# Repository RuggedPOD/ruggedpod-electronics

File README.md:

# RuggedPOD Electronic Design

This repository contains design for electronics, cables and connectors design.

Electonics design is done under [KiCad](http://kicad-pcb.org/), an open source electronics design automation suite.

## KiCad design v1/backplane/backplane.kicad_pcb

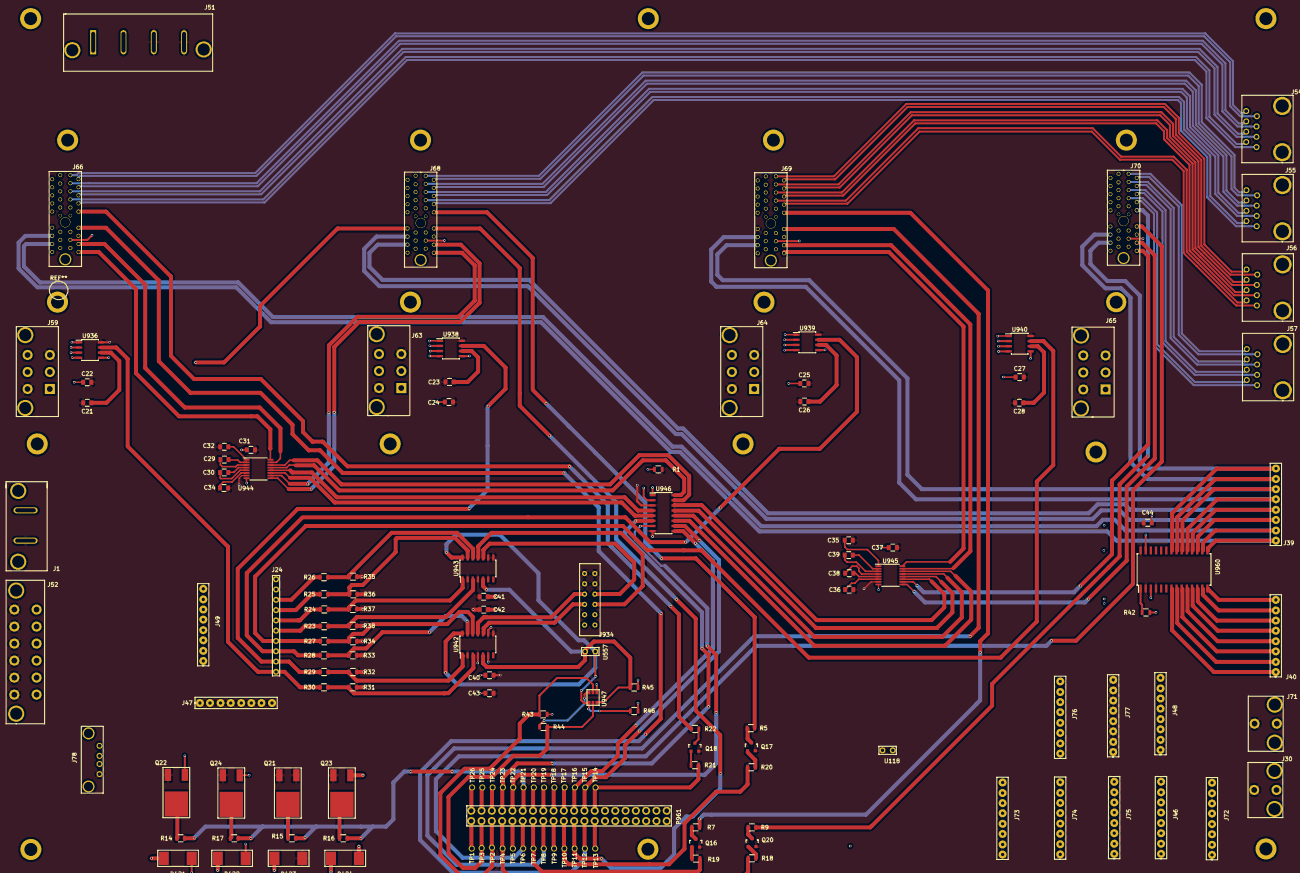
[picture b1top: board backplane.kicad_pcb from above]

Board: 4 copper layers, 141 parts (0 on the bottom side), 158 nets.

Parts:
C21, C23, C26, C28: 1n; C_0805
C22, C24, C25, C27, C29, C30, C31, C32, C34, C35, C36, C37, C38, C39, C40, C43: 0.1u; C_0805
C41, C42: 10u; C_0805
C44: 100n; C_0805
D421, D422, D423, D424: B520C-13-F; B520C
J1: Molex-1720420201; Molex172042-0201
J24: 10_Pin_Header; XG8V-1031
J30, J71: Molex-46999-0126; Molex46999-0126
J39, J40, J46, J47, J48, J49, J72, J73, J74, J75, J76, J77: SWITCH; XG8
J51: MOLEX172042-0402; Molex172042-0402
J52: MOLEX-39-28-9128; Molex_39-28-9128
J54, J55, J56, J57: MOLEX_85506-5001; Molex_85506-5001
J59, J63, J64, J65: 15-24-7060Molex; MOLEX15247060
J66, J68, J69, J70: FCI10018783-10000MLF; FCI_10018783-10000MLF
J78: 1734366-1; 1734366-1USB
J934: SWITCH934; FCI861400122YO2
P961: 0702464001; FCI702464001
Q16, Q17, Q18, Q20: bsr14; SOT-23
Q21, Q22, Q23, Q24: MJD112TF; MJD112
R1: 51; R_0805
R5, R7, R9, R22: 470; R_0805
R14, R15, R16, R17: 1K; R_0805
R18, R19, R20, R21: 2K; R_0805
R23, R24, R25, R26, R27, R28, R29, R30, R31, R32, R33, R34, R35, R36, R37, R38, R42: 10k; R_0805
R43, R44, R45, R46: 2.2K; R_0805
TP1, TP2, TP3, TP4, TP5, TP6, TP7, TP8, TP9, TP10, TP11, TP12, TP13, TP14, TP15, TP16, TP17, TP18, TP19, TP20, TP21, TP22, TP23, TP24, TP25, TP26: TP
U118, U557: Controler_Rasberry; XG8V-0231
U936, U938, U939, U940: ACS712ELCTR-20A-T; SOIC-8_3.9x4.9mm_Pitch1.27mm
U942, U943: MCP3424; SOIC-14_3.9x8.7mm_Pitch1.27mm
U944, U945: MAX3232; TSSOP-16_4.4x5mm_Pitch0.65mm
U946: MAX399; SOIC-16_3.9x9.9mm_Pitch1.27mm
U947: FDC6301N
U960: MCP23017; SOIC-28_7.5x17.9mm_Pitch1.27mm

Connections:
5VCC: C22.1, C24.1, C25.1, C27.1, C40.1, C41.1, C42.1, C43.1, C44.1, J24.9, J46.1, J46.2, J46.3, J46.4, J46.5, J46.6, J46.7, J46.8, J52.1, J52.3, J52.5, J71.1, J78.1, J934.1, J934.2, J934.7, J934.8, R42.1, R45.2, R46.1, U118.2, U936.1, U938.1, U939.1, U940.1, U960.3, U960.27
12VCC: D421.1, D422.1, D423.1, D424.1, J30.1, J48.1, J48.2, J48.3, J48.4, J48.5, J48.6, J48.7, J48.8, J52.2, J52.4, J52.6, J66.30, J68.30, J69.30, J70.30
24V_1: J59.1, J59.4, U936.4, U936.5
24V_2: J63.1, J63.4, U938.4, U938.5
24V_3: J64.1, J64.4, U939.4, U939.5
24V_4: J65.1, J65.4, U940.4, U940.5
24V_acdc: J1.1, J51.1, J51.2, U936.2, U936.3, U938.2, U938.3, U939.2, U939.3, U940.2, U940.3
+3V3: C31.1, C37.1, R1.1, R43.1, U944.8, U945.8, U946.1, U946.2, U947.3
APump_GND: D421.2, J66.23, Q22.3
APump_PWM: J39.1, J66.27, U960.15
APump_Sense: J39.2, J66.31, U960.16
A_Adr0: J934.10, U942.11
A_Adr1: J934.9, U942.10
A_ON/OFF: J66.20, R22.1
A_RESET: J66.24, P961.12, TP12.1
A_RX: J66.32, U944.15
A_RX_TTL: U944.13, U946.16
A_TD0+: J54.1, J66.16
A_TD0-: J54.5, J66.14
A_TD1+: J54.2, J66.12
A_TD1-: J54.6, J66.10
A_TD2+: J54.3, J66.8
A_TD2-: J54.7, J66.6
A_TD3+: J54.4, J66.4
A_TD3-: J54.8, J66.2
A_TX: J66.36, U944.16
A_TX_TTL: U944.14, U946.15
BPump_GND: D422.2, J68.23, Q24.3
BPump_PWM: J39.3, J68.27, U960.17
BPump_Sense: J39.4, J68.31, U960.18
B_Adr0: J934.3, U943.11
B_Adr1: J934.4, U943.10
B_ON/OFF: J68.20, R5.2
B_RESET: J68.24, P961.11, TP11.1
B_RX: J68.32, U944.9
B_RX_TTL: U944.11, U946.5
B_TD0+: J55.1, J68.16
B_TD0-: J55.5, J68.14
B_TD1+: J55.2, J68.12
B_TD1-: J55.6, J68.10
B_TD2+: J55.3, J68.8
B_TD2-: J55.7, J68.6
B_TD3+: J55.4, J68.4
B_TD3-: J55.8, J68.2
B_TX: J68.36, U944.10
B_TX_TTL: U944.12, U946.4
CPump_GND: C21.2, C22.2, C23.2, C24.2, C25.2, C26.2, C27.2, C28.2, C31.2, C32.2, C34.1, C35.2, C36.1, C37.2, C40.2, C41.2, C42.2, C43.2, C44.2, D423.2, J1.2, J24.10, J30.2, J47.1, J47.2, J47.3, J47.4, J47.5, J47.6, J47.7, J47.8, J51.3, J51.4, J52.7, J52.8, J52.9, J52.10, J52.11, J52.12, J54.9, J54.10, J55.9, J55.10, J56.9, J56.10, J57.9, J57.10, J59.3, J59.6, J63.3, J63.6, J64.3, J64.6, J65.3, J65.6, J69.23, J71.2, J77.1, J77.2, J77.3, J77.4, J77.5, J77.6, J77.7, J77.8, J78.4, J934.5, J934.6, J934.11, J934.12, Q16.2, Q17.2, Q18.2, Q20.2, Q21.2, Q21.3, Q22.2, Q23.2, Q24.2, R1.2, R31.2, R32.2, R33.2, R34.2, R35.2, R36.2, R37.2, R38.2, U118.1, U936.8, U938.8, U939.8, U940.8, U942.2, U942.4, U942.6, U942.8, U942.9, U943.2, U943.4, U943.6, U943.8, U943.9, U944.7, U945.7, U946.3, U946.8, U960.2, U960.4, U960.28
CPump_PWM: J39.5, J69.27, U960.19
CPump_Sense: J39.6, J69.31, U960.20
CS_1: J24.1, R30.1, U936.7
CS_2: J24.2, R29.1, U938.7
CS_3: J24.3, R28.1, U939.7
CS_4: J24.4, R27.1, U940.7
C_ON/OFF: J69.20, R7.2
C_RESET: J69.24, P961.8, TP8.1
C_RX: J69.32, U945.15
C_RX_TTL: U945.13, U946.12
C_TD0+: J56.1, J69.16
C_TD0-: J56.5, J69.14
C_TD1+: J56.2, J69.12
C_TD1-: J56.6, J69.10
C_TD2+: J56.3, J69.8
C_TD2-: J56.7, J69.6
C_TD3+: J56.4, J69.4
C_TD3-: J56.8, J69.2
C_TX: J69.36, U945.16
C_TX_TTL: U945.14, U946.11
ComAdd0: P961.32, TP15.1, U946.10
ComAdd1: P961.31, TP16.1, U946.9
DPump_GND: D424.2, J70.23, Q23.3
DPump_PWM: J39.7, J70.27, U960.21
DPump_Sense: J39.8, J70.31, U960.22
D_ON/OFF: J70.20, R9.2
D_RESET: J70.24, P961.6, TP6.1
D_RX: J70.32, U945.9
D_RX_TTL: U945.11, U946.14
D_TD0+: J57.1, J70.16
D_TD0-: J57.5, J70.14
D_TD1+: J57.2, J70.12
D_TD1-: J57.6, J70.10
D_TD2+: J57.3, J70.8
D_TD2-: J57.7, J70.6
D_TD3+: J57.4, J70.4
D_TD3-: J57.8, J70.2
D_TX: J70.36, U945.10
D_TX_TTL: U945.12, U946.13
GPA0: J40.1, U960.7
GPA1: J40.2, U960.8
GPA2: J40.3, U960.9
GPA3: J40.4, U960.10
GPA4: J40.5, U960.11
GPA5: J40.6, U960.12
GPA6: J40.7, U960.13
GPA7: J40.8, U960.14
unnamed: C21.1, U936.6
unnamed: C23.1, U938.6
unnamed: C26.1, U939.6
unnamed: C28.1, U940.6
unnamed: C29.1, U944.2
unnamed: C29.2, U944.3
unnamed: C30.1, U944.5
unnamed: C30.2, U944.4
unnamed: C32.1, U944.1
unnamed: C34.2, U944.6
unnamed: C35.1, U945.1
unnamed: C36.2, U945.6
unnamed: C38.1, U945.5
unnamed: C38.2, U945.4
unnamed: C39.1, U945.2
unnamed: C39.2, U945.3
unnamed: J24.5, R23.1
unnamed: J24.6, R24.1
unnamed: J24.7, R25.1
unnamed: J24.8, R26.1
unnamed: P961.1, TP1.1
unnamed: P961.4, R18.1, TP4.1
unnamed: P961.5, TP5.1
unnamed: P961.7, R19.1, TP7.1
unnamed: P961.9, TP9.1
unnamed: P961.10, R20.1, TP10.1
unnamed: P961.13, TP13.1
unnamed: P961.21, TP26.1
unnamed: P961.22, TP25.1
unnamed: P961.23, TP24.1
unnamed: P961.27, TP20.1
unnamed: P961.28, TP19.1
unnamed: P961.29, TP18.1
unnamed: P961.30, TP17.1
unnamed: P961.33, R21.2, TP14.1
unnamed: Q16.1, R19.2
unnamed: Q16.3, R7.1
unnamed: Q17.1, R20.2
unnamed: Q17.3, R5.1
unnamed: Q18.1, R21.1
unnamed: Q18.3, R22.2
unnamed: Q20.1, R18.2
unnamed: Q20.3, R9.1
unnamed: Q21.1, R15.1
unnamed: Q22.1, R14.1
unnamed: Q23.1, R16.1
unnamed: Q24.1, R17.1
unnamed: R23.2, R38.1, U943.3
unnamed: R24.2, R37.1, U943.1
unnamed: R25.2, R36.1, U943.13
unnamed: R26.2, R35.1, U943.12
unnamed: R27.2, R34.1, U942.12
unnamed: R28.2, R33.1, U942.13
unnamed: R29.2, R32.1, U942.1
unnamed: R30.2, R31.1, U942.3
unnamed: R42.2, U960.1
unnamed: R44.1, U947.1
unnamed: R45.1, U557.2, U942.5, U943.5, U947.6
unnamed: R46.2, U557.1, U942.14, U943.14, U947.4
Pump1/2/3/4: P961.26, R14.2, R15.2, R16.2, R17.2, TP21.1
RXD: P961.25, TP22.1, U946.7
SCL1: P961.2, R44.2, TP3.1, U947.5
SDA1: P961.3, R43.2, TP2.1, U947.2
TXD: P961.24, TP23.1, U946.6

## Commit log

2016-11-03 Init repository
2016-11-03 Add RuggedPOD backplane v1 electronic design
2016-11-03 Add .gitignore
2016-11-03 Add RuggedPOD connectic board v1
2016-11-03 Add RuggedPOD cables design v1
